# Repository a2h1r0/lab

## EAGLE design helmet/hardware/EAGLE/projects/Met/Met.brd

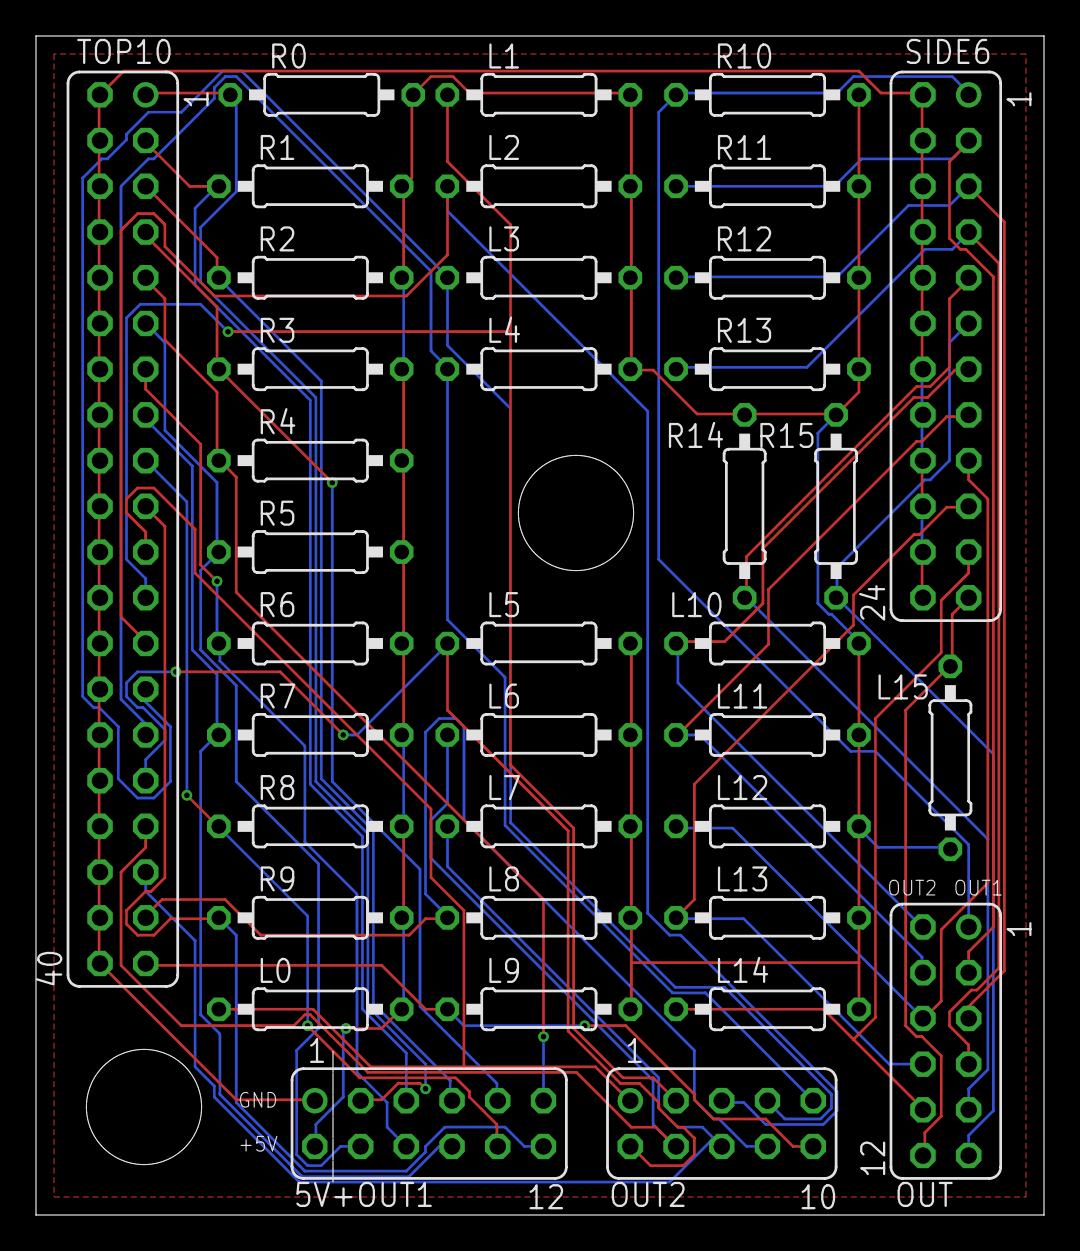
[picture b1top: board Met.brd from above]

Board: 2 copper layers, 56.0 x 65.5 mm, 37 parts (0 on the bottom side), 34 nets.

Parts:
5V+OUT1: FE06-2
L0, L1, L2, L3, L4, L5, L6, L7, L8, L9, L10, L11, L12, L13, L14, L15: 0207/10
OUT: FE06-2
OUT2: FE05-2
R0, R10: 10K; 0207/10
R1, R2, R3, R4, R5, R6, R7, R8, R9, R11, R12, R13, R14, R15: 0207/10
SIDE6: FE12-2
TOP10: FE20-2

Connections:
+5V: 5V+OUT1.2, L0.2, L1.2, L2.2, L3.2, L4.2, L5.2, L6.2, L7.2, L8.2, L9.2, L10.2, L11.2, L12.2, L13.2, L14.2, L15.2, R0.2, R1.2, R2.2, R3.2, R4.2, R5.2, R6.2, R7.2, R8.2, R9.2, R10.2, R11.2, R12.2, R13.2, R14.2, R15.2
GND: 5V+OUT1.1, SIDE6.2, SIDE6.4, SIDE6.6, SIDE6.8, SIDE6.10, SIDE6.12, SIDE6.14, SIDE6.16, SIDE6.18, SIDE6.20, SIDE6.22, SIDE6.24, TOP10.2, TOP10.4, TOP10.6, TOP10.8, TOP10.10, TOP10.12, TOP10.14, TOP10.16, TOP10.18, TOP10.20, TOP10.22, TOP10.24, TOP10.26, TOP10.28, TOP10.30, TOP10.32, TOP10.34, TOP10.36, TOP10.38, TOP10.40
unnamed: 5V+OUT1.7, R2.1, TOP10.5
unnamed: 5V+OUT1.8, R7.1, TOP10.15
unnamed: 5V+OUT1.6, R6.1, TOP10.13
unnamed: 5V+OUT1.4, R5.1, TOP10.11
unnamed: 5V+OUT1.3, R0.1, TOP10.1
unnamed: 5V+OUT1.5, R1.1, TOP10.3
unnamed: 5V+OUT1.9, R3.1, TOP10.7
unnamed: 5V+OUT1.11, R4.1, TOP10.9
unnamed: OUT.5, R12.1, SIDE6.5
unnamed: L12.1, OUT.6, SIDE6.17
unnamed: 5V+OUT1.10, R8.1, TOP10.17
unnamed: OUT.3, R11.1, SIDE6.3
unnamed: L0.1, OUT2.1, TOP10.21
unnamed: L1.1, OUT2.3, TOP10.23
unnamed: L3.1, OUT2.7, TOP10.27
unnamed: L4.1, OUT2.9, TOP10.29
unnamed: L5.1, OUT2.2, TOP10.31
unnamed: L6.1, OUT2.4, TOP10.33
unnamed: L7.1, OUT2.6, TOP10.35
unnamed: L8.1, OUT2.8, TOP10.37
unnamed: L2.1, OUT2.5, TOP10.25
unnamed: 5V+OUT1.12, R9.1, TOP10.19
unnamed: L9.1, OUT2.10, TOP10.39
unnamed: OUT.1, R10.1, SIDE6.1
unnamed: OUT.7, R13.1, SIDE6.7
unnamed: OUT.9, R14.1, SIDE6.9
unnamed: OUT.11, R15.1, SIDE6.11
unnamed: L10.1, OUT.2, SIDE6.13
unnamed: L11.1, OUT.4, SIDE6.15
unnamed: L13.1, OUT.8, SIDE6.19
unnamed: L14.1, OUT.10, SIDE6.21
unnamed: L15.1, OUT.12, SIDE6.23

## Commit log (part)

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2024-03-03 remove
2024-03-03 collect data
2024-03-03 preprocess
2024-04-12 データの移動
2024-04-12 archive jins project
2024-04-28 upload
2024-04-30 delete
2024-05-12 HASCA2024テンプレート流し込み
2024-05-18 make data
2024-05-18 rename
2024-05-18 make feature
2024-06-16 calibration
2024-06-16 move
2024-06-16 reanme
2024-06-16 exam
2024-06-17 get data
2024-06-17 get_data
2024-06-17 create data
2024-06-17 create
2024-06-19 rwmovw
2024-06-21 collect
2024-06-22 dropna
2024-07-03 make test
2024-07-04 updatw
2024-07-05 remove test data
2024-07-11 split
2024-07-14 remoce
2024-07-27 upload camera ready
